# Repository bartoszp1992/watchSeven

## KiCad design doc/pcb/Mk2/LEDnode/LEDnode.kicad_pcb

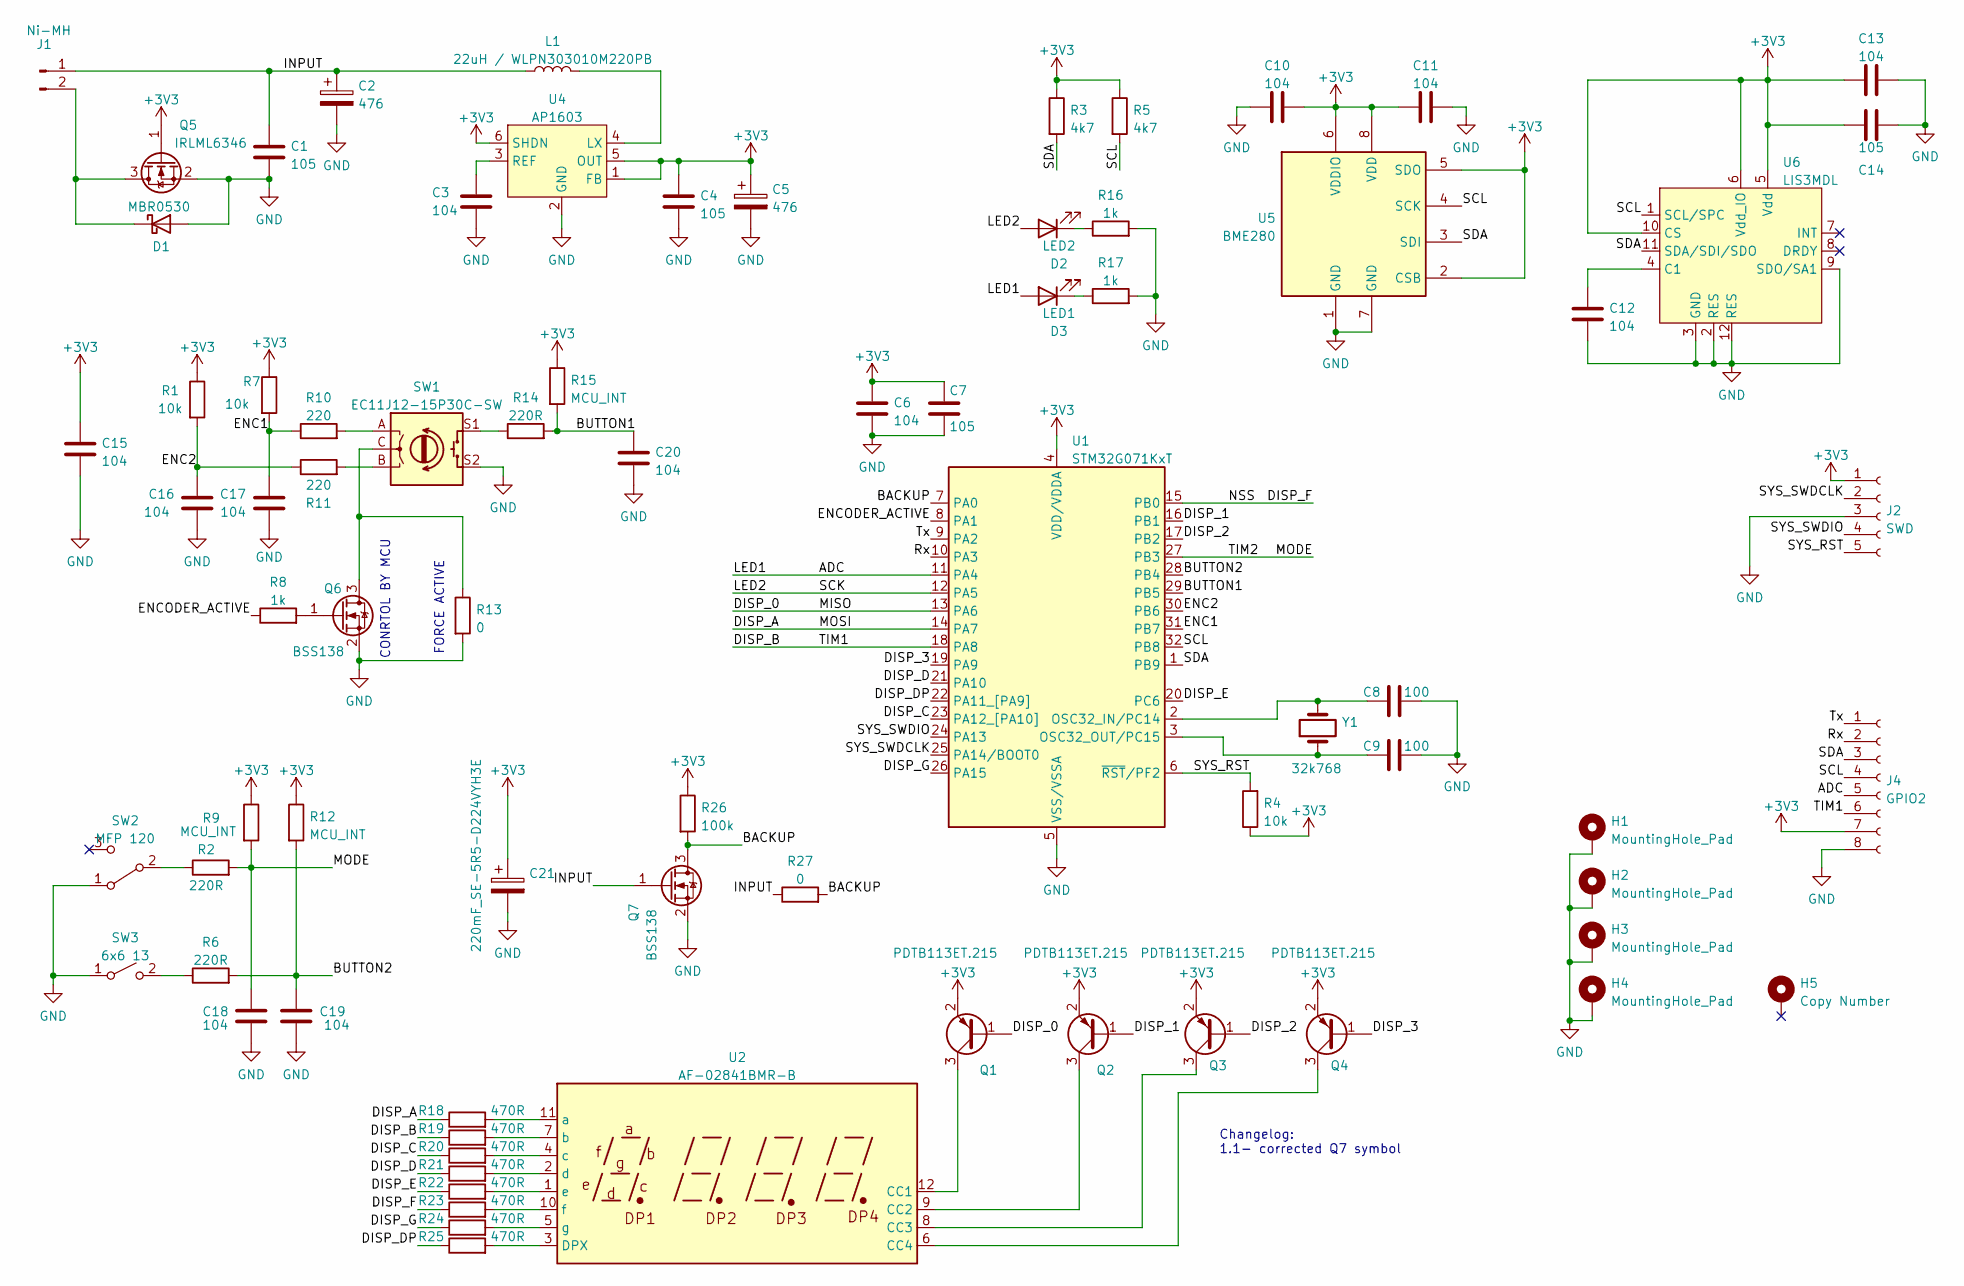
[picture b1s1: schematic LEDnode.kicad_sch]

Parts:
C1, C4, C7, C14: 105; C_0603_1608Metric
C2, C5: 476; CP_Elec_5x4.5
C3, C6, C10, C11, C12, C13, C15, C16, C17, C18, C19, C20: 104; C_0603_1608Metric
C8, C9: 100; C_0603_1608Metric
C21: 220mF_SE-5R5-D224VYH3E; C_Super_D11.2mm_H5.1mm_P10.5mm
D1: MBR0530; D_SOD-123
D2: LED2; LED_0603_1608Metric
D3: LED1; LED_0603_1608Metric
H1, H2, H3, H4: MountingHole_Pad; WirePad 4mm^2 Rect
H5: Copy Number; number
J1: Ni-MH; BC-0401 AAA R3
J2: SWD; PinHeader_1x05_P1.257_Vertical
J4: GPIO2; PinHeader_1x08_P2.54mm_Vertical
L1: 22uH / WLPN303010M220PB; L_Abracon_ASPI-3012S
Q1, Q2, Q3, Q4: PDTB113ET.215; SOT-23
Q5: IRLML6346; SOT-23
Q6, Q7: BSS138; SOT-23
R1, R4, R7: 10k; R_0603_1608Metric
R2, R6, R14: 220R; R_0603_1608Metric
R3, R5: 4k7; R_0603_1608Metric
R8, R16, R17: 1k; R_0603_1608Metric
R9, R12, R15: MCU_INT; R_0603_1608Metric
R10, R11: 220; R_0603_1608Metric
R13, R27: 0; R_0603_1608Metric
R18, R19, R20, R21, R22, R23, R24, R25: 470R; R_0603_1608Metric
R26: 100k; R_0603_1608Metric
SW1: EC11J12-15P30C-SW
SW2: MFP 120
SW3: 6x6 13; SW_PUSH_6mm_H13mm
U1: STM32G071KxT; LQFP-32_7x7mm_P0.8mm
U2: AF-02841BMR-B; LED 7.2mm SMD
U4: AP1603; SOT-23-6
U5: BME280; Bosch_LGA-8_2.5x2.5mm_P0.65mm_ClockwisePinNumbering
U6: LIS3MDL; LGA-12_2x2mm_P0.5mm
Y1: 32k768; Crystal_D2.00mm_L6.00mm

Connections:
+3V3: C4.1, C5.1, C6.1, C7.1, C10.1, C11.1, C13.1, C14.1, C15.1, C21.1, J2.1, J4.7, Q1.2 (E), Q2.2 (E), Q3.2 (E), Q4.2 (E), Q5.1 (G), R1.1, R3.1, R4.1, R5.1, R7.1, R9.1, R12.1, R15.1, R26.1, U1.4 (VDD/VDDA), U4.1 (FB), U4.5 (OUT), U4.6 (SHDN), U5.2 (CSB), U5.5 (SDO), U5.6 (VDDIO), U5.8 (VDD), U6.5 (Vdd), U6.6 (Vdd_IO), U6.10 (CS)
/ADC: D3.2 (A), J4.5, U1.11 (PA4)
/BACKUP: Q7.3 (D), R26.2, R27.2, U1.7 (PA0)
/BUTTON1: C20.1, R14.2, R15.2, U1.29 (PB5)
/BUTTON2: C19.1, R6.2, R12.2, U1.28 (PB4)
/DISP_0: Q1.1 (B), U1.13 (PA6)
/DISP_1: Q2.1 (B), U1.16 (PB1)
/DISP_2: Q3.1 (B), U1.17 (PB2)
/DISP_3: Q4.1 (B), U1.19 (PA9)
/DISP_A: R18.1, U1.14 (PA7)
/DISP_B: J4.6, R19.1, U1.18 (PA8)
/DISP_C: R20.1, U1.23 (PA12_[PA10])
/DISP_D: R21.1, U1.21 (PA10)
/DISP_DP: R25.1, U1.22 (PA11_[PA9])
/DISP_E: R22.1, U1.20 (PC6)
/DISP_F: R23.1, U1.15 (PB0)
/DISP_G: R24.1, U1.26 (PA15)
/ENC1: C17.1, R7.2, R10.1, U1.31 (PB7)
/ENC2: C16.2, R1.2, R11.1, U1.30 (PB6)
/ENCODER_ACTIVE: R8.1, U1.8 (PA1)
/INPUT: C1.1, C2.1, J1.1, L1.1, Q7.1 (G), R27.1
/LED2: D2.2 (A), U1.12 (PA5)
/MODE: C18.1, R2.2, R9.2, U1.27 (PB3)
/Rx: J4.2, U1.10 (PA3)
/SCL: J4.4, R5.2, U1.32 (PB8), U5.4 (SCK), U6.1 (SCL/SPC)
/SDA: J4.3, R3.2, U1.1 (PB9), U5.3 (SDI), U6.11 (SDA/SDI/SDO)
/SYS_RST: J2.5, R4.2, U1.6 (~RST/PF2)
/SYS_SWDCLK: J2.2, U1.25 (PA14/BOOT0)
/SYS_SWDIO: J2.4, U1.24 (PA13)
/Tx: J4.1, U1.9 (PA2)
GND: C1.2, C2.2, C3.2, C4.2, C5.2, C6.2, C7.2, C8.2, C9.2, C10.2, C11.2, C12.2, C13.2, C14.2, C15.2, C16.1, C17.2, C18.2, C19.2, C20.2, C21.2, D1.2 (A), H1.1, H2.1, H3.1, H4.1, J2.3, J4.8, Q5.2 (S), Q6.2 (S), Q7.2 (S), R13.2, R16.2, R17.2, SW1.S2, SW2.1 (A), SW3.1 (A), U1.5 (VSS/VSSA), U4.2 (GND), U5.1 (GND), U5.7 (GND), U6.2 (RES), U6.3 (GND), U6.9 (SDO/SA1), U6.12 (RES)
unnamed: C3.1, U4.3 (REF)
unnamed: C8.1, U1.2 (OSC32_IN/PC14), Y1.2
unnamed: C9.1, U1.3 (OSC32_OUT/PC15), Y1.1
unnamed: C12.1, U6.4 (C1)
unnamed: D1.1 (K), J1.2, Q5.3 (D)
unnamed: D2.1 (K), R16.1
unnamed: D3.1 (K), R17.1
unnamed: L1.2, U4.4 (LX)
unnamed: Q1.3 (C), U2.12 (CC1)
unnamed: Q2.3 (C), U2.9 (CC2)
unnamed: Q3.3 (C), U2.8 (CC3)
unnamed: Q4.3 (C), U2.6 (CC4)
unnamed: Q6.1 (G), R8.2
unnamed: Q6.3 (D), R13.1, SW1.C
unnamed: R2.1, SW2.2 (B)
unnamed: R6.1, SW3.2 (B)
unnamed: R10.2, SW1.A
unnamed: R11.2, SW1.B
unnamed: R14.1, SW1.S1
unnamed: R18.2, U2.11 (a)
unnamed: R19.2, U2.7 (b)
unnamed: R20.2, U2.4 (c)
unnamed: R21.2, U2.2 (d)
unnamed: R22.2, U2.1 (e)
unnamed: R23.2, U2.10 (f)
unnamed: R24.2, U2.5 (g)
unnamed: R25.2, U2.3 (DPX)

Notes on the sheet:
FORCE ACTIVE
CONRTOL BY MCU
Changelog: 1.1- corrected Q7 symbol

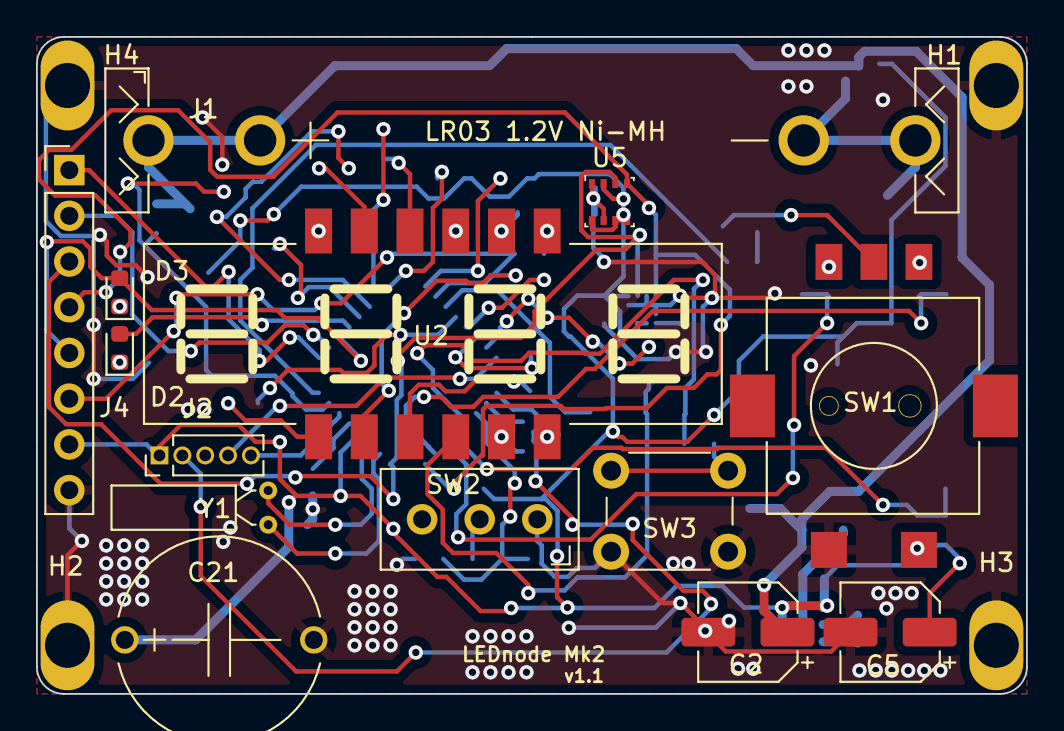
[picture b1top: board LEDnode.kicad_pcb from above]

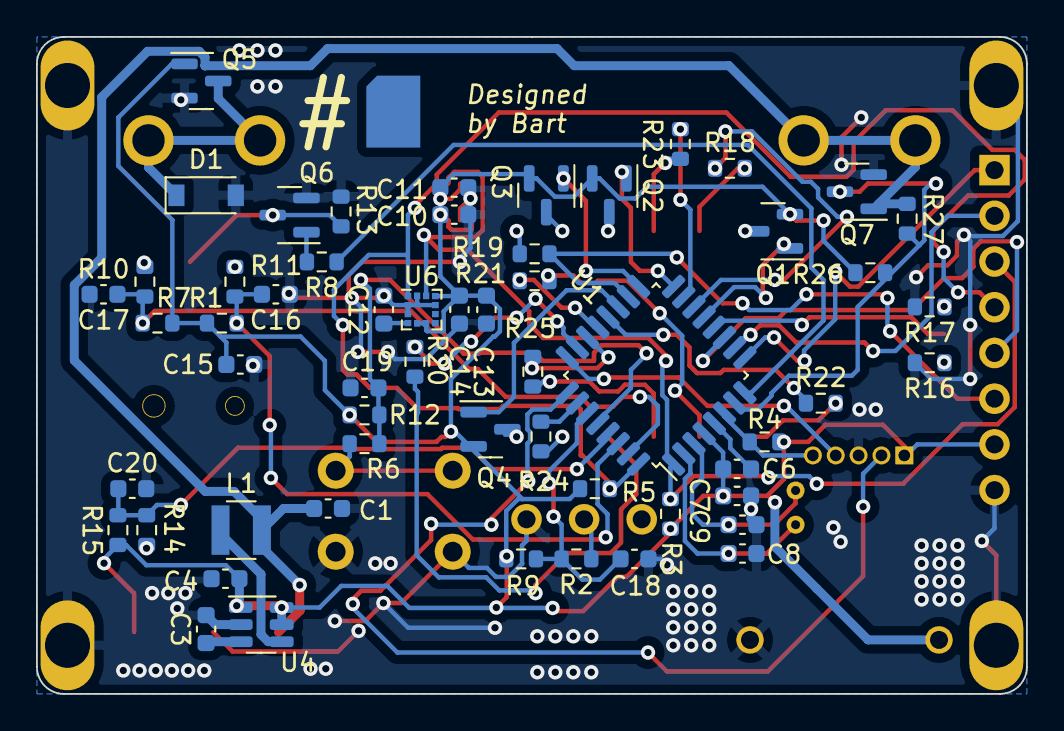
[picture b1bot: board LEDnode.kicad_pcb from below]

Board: 2 copper layers, 55.0 x 36.5 mm, 76 parts (58 on the bottom side), 58 nets.

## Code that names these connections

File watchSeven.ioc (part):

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Mcu.Name=STM32G071K(6-8-B)Tx
Mcu.Package=LQFP32
Mcu.UserName=STM32G071KBTx
PA0.GPIOParameters=GPIO_PuPd,GPIO_Label,GPIO_ModeDefaultEXTI
PA0.GPIO_Label=BACKUP
PA0.GPIO_ModeDefaultEXTI=GPIO_MODE_IT_RISING
PA0.GPIO_PuPd=GPIO_NOPULL
PA0.Signal=GPXTI0
PA1.GPIOParameters=GPIO_Label
PA1.GPIO_Label=ENCODER_ACTIVE
PA1.Signal=GPIO_Output
PA10.GPIOParameters=PinState,GPIO_Label
PA10.GPIO_Label=DISP_D
PA10.PinState=GPIO_PIN_SET
PA10.Signal=GPIO_Output
PA11\ [PA9].GPIOParameters=PinState,GPIO_Label
PA11\ [PA9].GPIO_Label=DISP_DP
PA11\ [PA9].PinState=GPIO_PIN_SET
PA11\ [PA9].Signal=GPIO_Output
PA12\ [PA10].GPIOParameters=PinState,GPIO_Label
PA12\ [PA10].GPIO_Label=DISP_C
PA12\ [PA10].PinState=GPIO_PIN_SET
PA12\ [PA10].Signal=GPIO_Output
PA13.Mode=Serial_Wire
PA13.Signal=SYS_SWDIO
PA14-BOOT0.Mode=Serial_Wire
PA14-BOOT0.Signal=SYS_SWCLK
PA15.GPIOParameters=PinState,GPIO_Label
PA15.GPIO_Label=DISP_G
PA15.PinState=GPIO_PIN_SET
PA15.Signal=GPIO_Output
PA2.Mode=Asynchronous
PA2.Signal=USART2_TX
PA3.Mode=Asynchronous
PA3.Signal=USART2_RX
PA4.GPIOParameters=GPIO_Label
PA4.GPIO_Label=LED_STANDBY
PA4.Signal=GPIO_Output
PA5.GPIOParameters=GPIO_Label
PA5.GPIO_Label=LED_WRITE
PA5.Signal=GPIO_Output
PA6.GPIOParameters=GPIO_Speed,PinState,GPIO_Label
PA6.GPIO_Label=DISP_0
PA6.GPIO_Speed=GPIO_SPEED_FREQ_LOW
PA6.PinState=GPIO_PIN_SET
PA6.Signal=GPIO_Output
PA7.GPIOParameters=PinState,GPIO_Label
PA7.GPIO_Label=DISP_A
PA7.PinState=GPIO_PIN_SET
PA7.Signal=GPIO_Output
PA8.GPIOParameters=PinState,GPIO_Label
PA8.GPIO_Label=DISP_B
PA8.PinState=GPIO_PIN_SET
PA8.Signal=GPIO_Output
PA9.GPIOParameters=PinState,GPIO_Label
PA9.GPIO_Label=DISP_3
PA9.PinState=GPIO_PIN_SET
PA9.Signal=GPIO_Output
PB0.GPIOParameters=PinState,GPIO_Label
PB0.GPIO_Label=DISP_F
PB0.PinState=GPIO_PIN_SET
PB0.Signal=GPIO_Output
PB1.GPIOParameters=PinState,GPIO_Label
PB1.GPIO_Label=DISP_1
PB1.PinState=GPIO_PIN_SET
PB1.Signal=GPIO_Output
PB2.GPIOParameters=PinState,GPIO_Label
PB2.GPIO_Label=DISP_2
PB2.PinState=GPIO_PIN_SET
PB2.Signal=GPIO_Output
PB3.GPIOParameters=GPIO_PuPd,GPIO_Label,GPIO_ModeDefaultEXTI
PB3.GPIO_Label=MODE
PB3.GPIO_ModeDefaultEXTI=GPIO_MODE_IT_RISING_FALLING
PB3.GPIO_PuPd=GPIO_PULLUP
PB3.Signal=GPXTI3
PB4.GPIOParameters=GPIO_PuPd,GPIO_Label,GPIO_ModeDefaultEXTI
PB4.GPIO_Label=BUTTON2
PB4.GPIO_ModeDefaultEXTI=GPIO_MODE_IT_FALLING
PB4.GPIO_PuPd=GPIO_PULLUP
PB4.Signal=GPXTI4
PB5.GPIOParameters=GPIO_PuPd,GPIO_Label,GPIO_ModeDefaultEXTI
PB5.GPIO_Label=BUTTON1
PB5.GPIO_ModeDefaultEXTI=GPIO_MODE_IT_FALLING
PB5.GPIO_PuPd=GPIO_PULLUP
PB5.Signal=GPXTI5
PB6.GPIOParameters=GPIO_PuPd,GPIO_Label,GPIO_ModeDefaultEXTI
PB6.GPIO_Label=ENC1
PB6.GPIO_ModeDefaultEXTI=GPIO_MODE_IT_RISING_FALLING
PB6.GPIO_PuPd=GPIO_NOPULL
PB6.Signal=GPXTI6
PB7.GPIOParameters=GPIO_PuPd,GPIO_Label,GPIO_ModeDefaultEXTI
PB7.GPIO_Label=ENC2
PB7.GPIO_ModeDefaultEXTI=GPIO_MODE_IT_RISING_FALLING
PB7.GPIO_PuPd=GPIO_NOPULL
PB7.Signal=GPXTI7
PB8.Mode=I2C
PB8.Signal=I2C1_SCL
PB9.Mode=I2C
PB9.Signal=I2C1_SDA
PC14-OSC32_IN\ (PC14).Mode=LSE-External-Oscillator
PC14-OSC32_IN\ (PC14).Signal=RCC_OSC32_IN
PC15-OSC32_OUT\ (PC15).Mode=LSE-External-Oscillator
PC15-OSC32_OUT\ (PC15).Signal=RCC_OSC32_OUT
PC6.GPIOParameters=PinState,GPIO_Label
PC6.GPIO_Label=DISP_E
PC6.PinState=GPIO_PIN_SET
PC6.Signal=GPIO_Output
RCC.HSE_VALUE=8000000
RCC.SYSCLKFreq_VALUE=64000000
RCC.SYSCLKSource=RCC_SYSCLKSOURCE_PLLCLK
board=custom

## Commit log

2022-04-16 initial
2022-04-16 initial with license
2022-04-16 almost working menu
2022-04-17 working menu
2022-04-18 working watch
2022-04-19 working clock set
2022-04-20 working chronograph, designed PCB
2022-04-22 added segment resistors
2022-04-25 working thermometer
2022-04-26 working temperature correction
2022-04-28 almost working bme280
2022-04-30 corrected bme280 lib
2022-05-01 working altimeter and humidity
2022-05-03 working eeprom emulation
2022-05-03 corrected license
2022-05-07 new pcb
2022-05-08 mk2 flag sleep corrected
2022-05-08 properly working standby LED
2022-05-14 mode as status
2022-05-27 corrected backup transistor
2022-06-17 fixed chronop bug
2022-06-22 magnetometer support
2023-11-02 control commit
